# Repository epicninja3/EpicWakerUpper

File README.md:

# EpicWakerUpper
EpicWakerUpper is an alarm clock powered by a Seeed XIAO ESP32C3. Additionally, this alarm clock features 6 key switches to make selections on its 2.25-inch TFT screen.

## Features:
+ 6 key switches to navigate throughout the clock system
+ Displays weather, can set an alarm, and can set a timer
+ Wakes you up through sound produced by the buzzer
+ 3D Printed case to make it look good!

## CAD

## PCB

## PCB Schematic

## PCB 3D Model
# Top

# Bottom

## Materials/BOM

+ 1x Seeed XIAO ESP32C3
+ 1x 3.3V Piezo Buzzer
+ 6x MX-Style Keyboard Switches
+ 6x White Blank DSA Keycaps
+ 6x Through-Hole 1N4148 Diodes
+ 1x 2.25in TFT Screen
+ 1x 3.3V Piezo Buzzer
+ 1x 2.54mm 8 Pin Male Header
+ 8x 20cm Female-Female Jumper Wires

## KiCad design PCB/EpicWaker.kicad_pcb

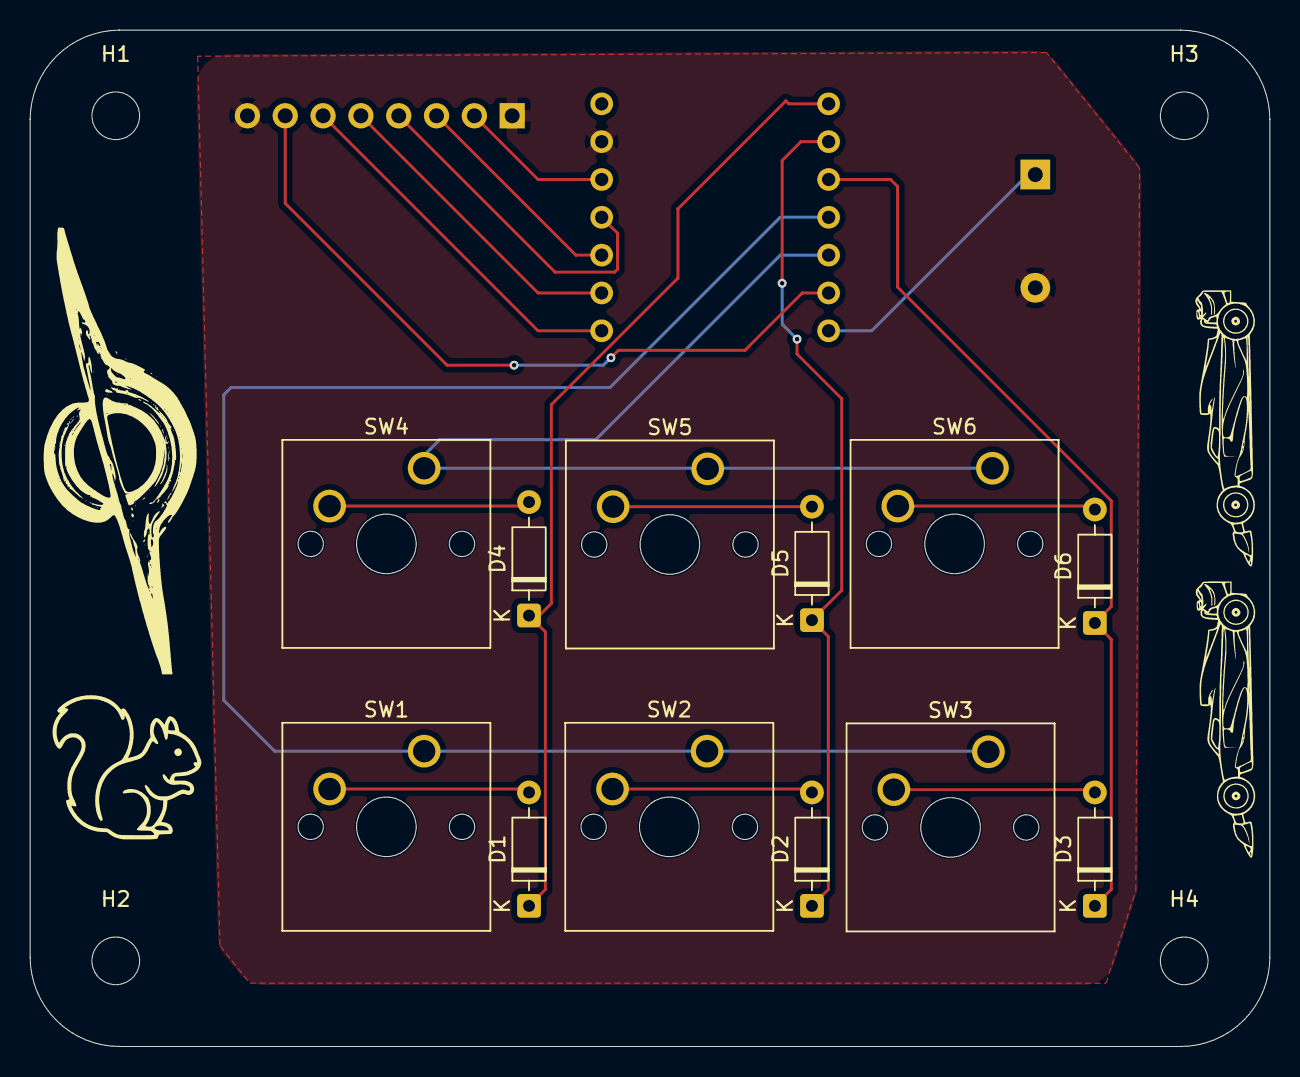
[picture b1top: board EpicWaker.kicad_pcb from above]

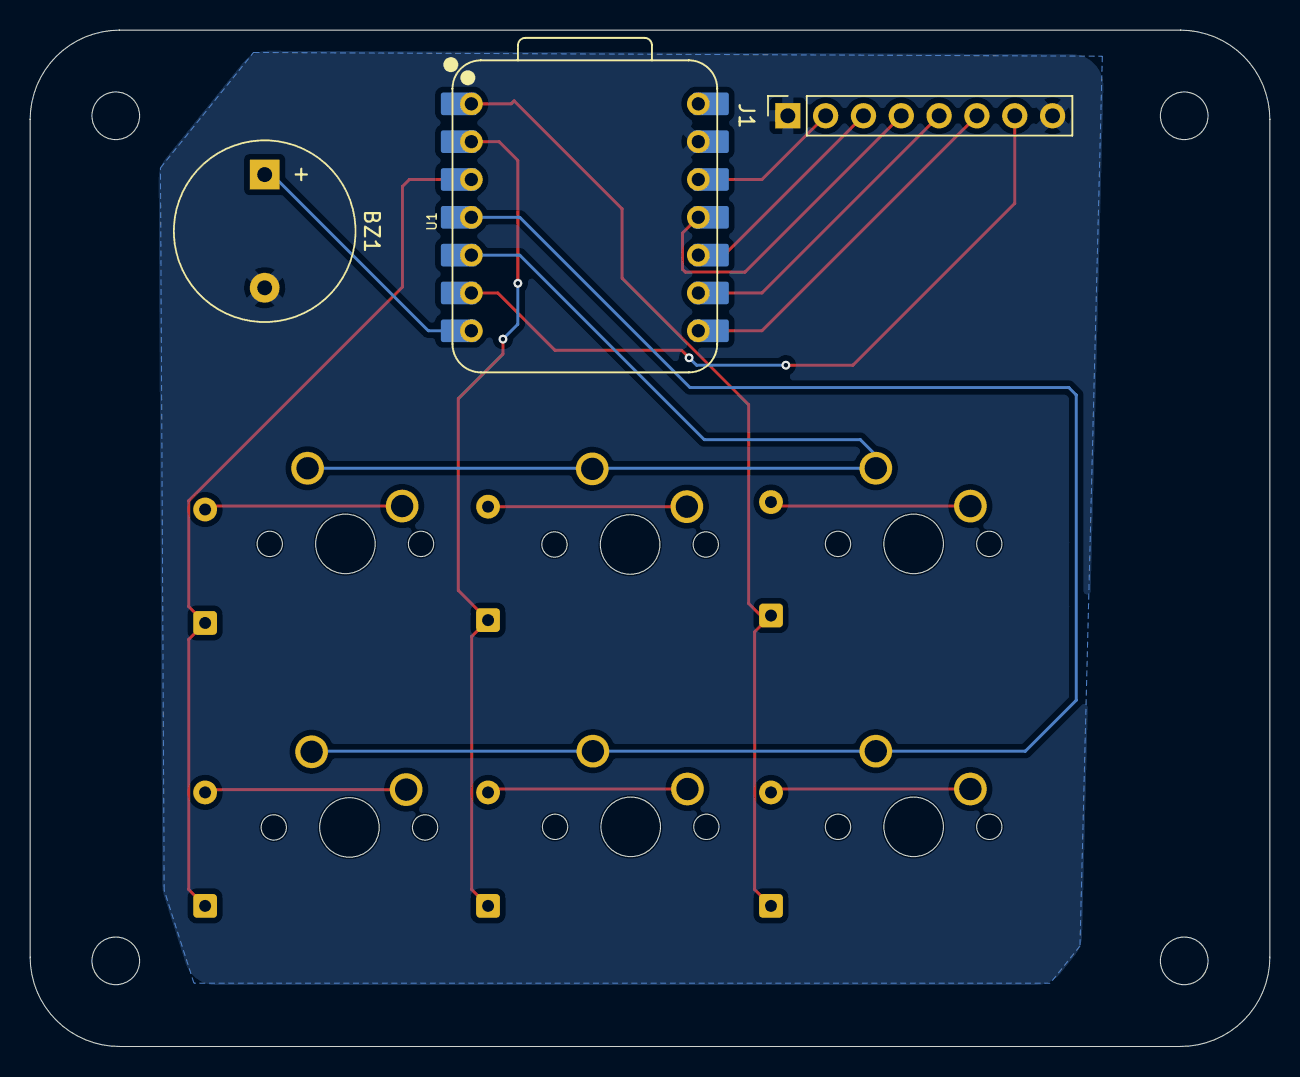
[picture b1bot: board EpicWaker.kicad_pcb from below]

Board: 2 copper layers, 83.2 x 68.2 mm, 19 parts (3 on the bottom side), 19 nets.

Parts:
BZ1: Buzzer; Buzzer_12x9.5RM7.6
D1, D2, D3, D4, D5, D6: D; D_DO-35_SOD27_P7.62mm_Horizontal
H1, H2, H3, H4: MountingHole; MountingHole_3.2mm_M3
J1: Conn_01x08_Pin; PinSocket_1x08_P2.54mm_Vertical
SW1, SW2, SW3, SW4, SW5, SW6: SW_Push; SW_Cherry_MX_1.00u_PCB
U1: XIAO-ESP32-C3-SMD; XIAO-ESP32-C3-DIP

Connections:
+3V3: J1.2, U1.12 (3V3_OUT)
COL 0: SW1.1, SW2.1, SW3.1, U1.4 (D3)
COL 1: SW4.1, SW5.1, SW6.1, U1.5 (D4)
CS: J1.7, U1.6 (D5)
DC: J1.6, U1.8 (D7)
GND: BZ1.2 (-), J1.1, J1.8, U1.13 (GND)
unnamed: BZ1.1 (+), U1.7 (D6)
unnamed: D1.2 (A), SW1.2
unnamed: D2.2 (A), SW2.2
unnamed: D3.2 (A), SW3.2
unnamed: D4.2 (A), SW4.2
unnamed: D5.2 (A), SW5.2
unnamed: D6.2 (A), SW6.2
ROW 0: D1.1 (K), D4.1 (K), U1.1 (D0)
ROW 1: D2.1 (K), D5.1 (K), U1.2 (D1)
ROW 2: D3.1 (K), D6.1 (K), U1.3 (D2)
RST: J1.5, U1.9 (D8)
SCL: J1.3, U1.10 (D9/BOOT)
SDA: J1.4, U1.11 (D10)
